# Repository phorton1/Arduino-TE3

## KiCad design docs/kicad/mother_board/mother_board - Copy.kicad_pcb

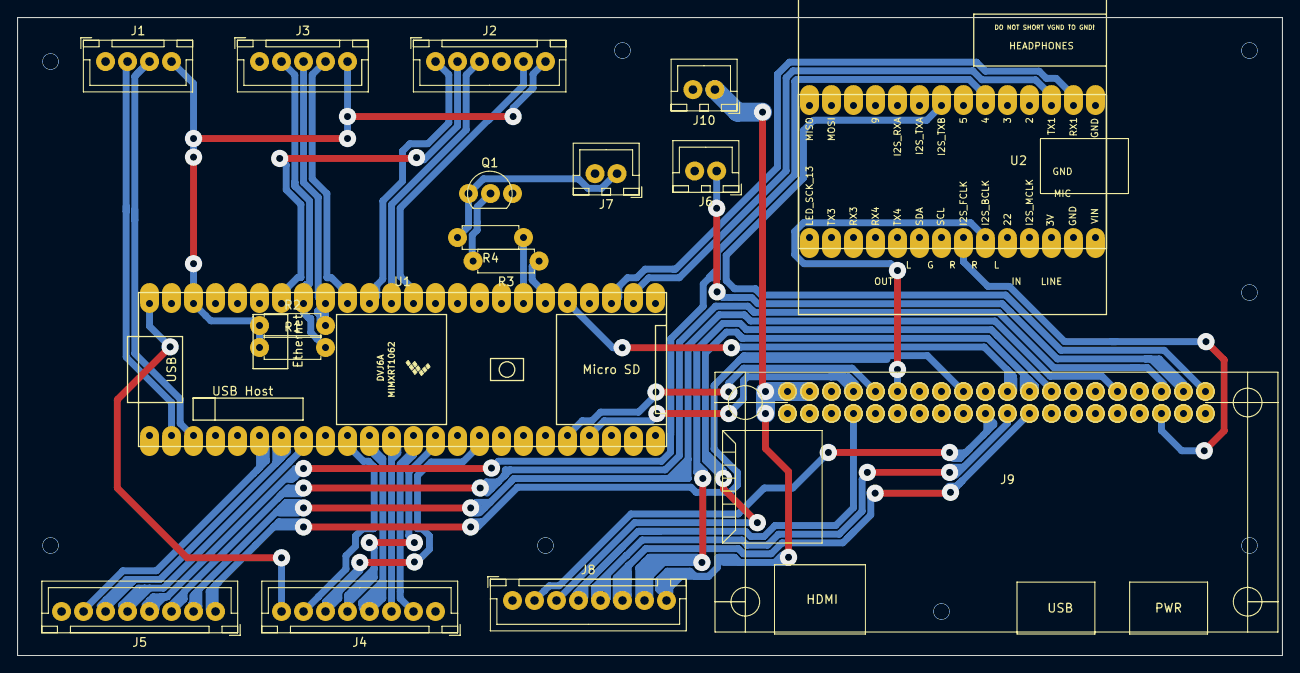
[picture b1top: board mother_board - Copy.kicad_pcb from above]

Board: 2 copper layers, 146.1 x 73.7 mm, 17 parts (0 on the bottom side), 45 nets.

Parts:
J1: DBG_SERIAL; myJSTx04
J2: ROW_BOARDS; myJSTx06
J3: ROTARIES; myJSTx05
J4: TE_DISPLAY; myJSTx08
J5: EXT_LEDS; myJSTx08
J6: I2S_TXB; myJSTx02
J7: RPI_RUN; myJSTx02
J8: RPI_DISPLAY; myJSTx08
J9: rpi_connector; rpi_zero_2w
J10: rPi_5V; myJSTx02
Q1: BC547; myTransistor
R1, R2, R3: 1K; myResistor
R4: 220; myResistor
U1: myTeensy4.1; teensy41
U2: teensyAudioRevD; audioShieldRevD

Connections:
+5V: J8.8, J9.2, J9.4, J10.1
BTN_CLK: J2.5, U1.36
BTN_DIN: J2.3, U1.37
BTN_SENSE: J2.1, U1.38
GND: J1.1, J2.4, J3.1, J4.1, J5.8, J8.1, J9.6, J9.9, J9.14, J9.20, J9.25, J9.30, J9.34, J9.39, J10.2, Q1.3, U1.1, U1.34, U1.47, U2.1, U2.27
I2S_BCLK: J9.12, U2.23
I2S_FCLK: J9.35, U2.22
I2S_RXB: J9.40, U2.8
I2S_TXB: J6.1, J9.38
LED_AUDIO_BUSY: J5.4, U2.6
LED_DIN: J2.2, U1.42
LED_RPI_BUSY: J5.1, J9.18
LED_RPI_I2S_RX: J5.2, J9.32
LED_RPI_I2S_TX: J5.3, J9.36
LED_RPI_READY: J5.5, U1.8
LED_RPI_RUN: J5.6, U1.7
LED_T3_BUSY: J5.7, U1.6
unnamed: Q1.2, R3.2
PI_REBOOT: R3.1, U1.30
ROT_INT: J3.4, U1.39
RPI_LCD_CS: J8.3, J9.24
RPI_LCD_DC: J8.4, J9.7
RPI_MISO: J8.5, J9.21
RPI_MOSI: J8.2, J9.19
RPI_READY: J9.22, U1.29
RPI_RUN: J7.1, Q1.1, R4.2
RPI_SCLK: J8.6, J9.23
RPI_T_CS: J8.7, J9.26
SENS_PI_RUN: R4.1, U1.31
T41_3V3: J1.4, J2.6, J3.5, R1.1, R2.1, U1.46
T41_5V: J4.8, U1.48
T41_LCD_CS: J4.3, U1.12
T41_LCD_DC: J4.4, U1.11
T41_MISO: J4.5, U1.14
T41_MOSI: J4.2, U1.13
T41_RX1: J1.2, U1.2
T41_RX7: J9.8, U1.21
T41_RX8: U1.26, U2.3
T41_SCL: J3.2, R1.2, U1.41
T41_SCLK: J4.6, U1.16
T41_SDA: J3.3, R2.2, U1.40
T41_TX1: J1.3, U1.3
T41_TX7: J9.10, U1.20
T41_TX8: U1.27, U2.2
T41_T_CS: J4.7, U1.10

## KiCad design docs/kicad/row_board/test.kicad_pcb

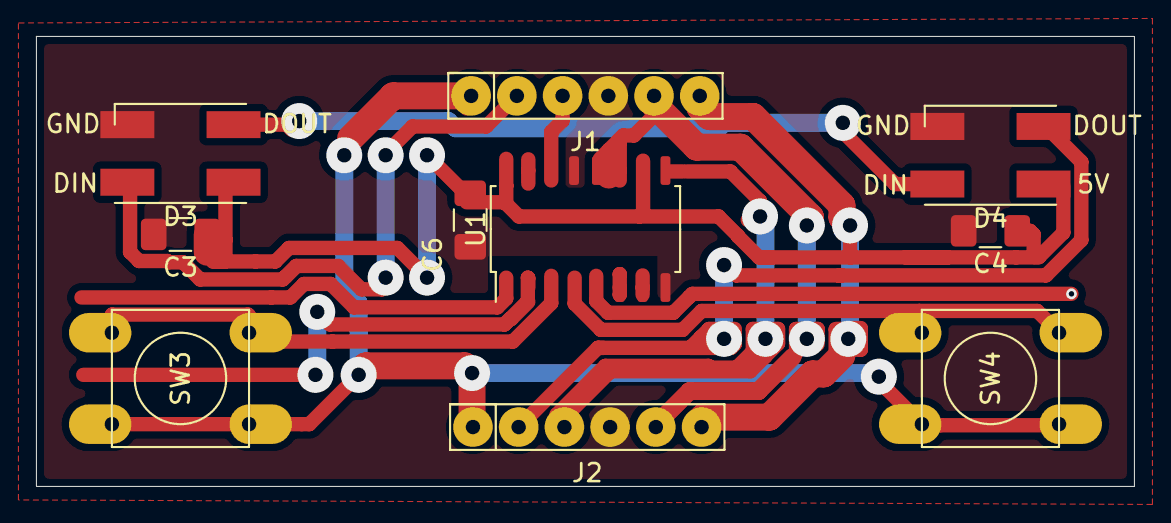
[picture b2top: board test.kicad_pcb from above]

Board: 2 copper layers, 61.0 x 25.0 mm, 10 parts (0 on the bottom side), 11 nets.

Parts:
C3, C4: 100nf; C_1206_3216Metric_Pad1.42x1.75mm_HandSolder
C6: 10uf; C_1206_3216Metric_Pad1.42x1.75mm_HandSolder
D3, D4: WS2812B; myWS2812
J1, J2: Conn_01x06; my6Pin-08mm
SW3, SW4: SW1; mySwitchSoft
U1: 74HC595; SOIC-16_4.55x10.3mm_P1.27mm

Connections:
+5V: C3.1, C4.1, C6.1, D3.1, D4.1, J1.6, J2.6, U1.10, U1.16
BTN_CLK: J1.5, J2.5, U1.11, U1.12
BTN_DIN: J1.3, U1.14
BTN_DOUT: J2.3, U1.9
BTN_SENSE: J1.1, J2.1, SW3.2, SW4.2
GND: C3.2, C4.2, C6.2, D3.3, D4.3, J1.4, J2.4, U1.8, U1.13
LED_DIN: D3.4, J1.2
LED_DOUT: D4.2, J2.2
unnamed: D3.2, D4.4
unnamed: SW3.1, U1.3
unnamed: SW4.1, U1.4
